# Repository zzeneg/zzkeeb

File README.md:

# zzkeeb

Shared library for my keyboard components

## KiCad

#### Installation
Go to KiCad, `Preferences` -> `Configure Paths`, add new row with name `ZZKEEB` and path to `zzkeeb/kicad`

#### Included projects

- https://github.com/sadekbaroudi/fingerpunch
- https://github.com/foostan/kbd
- https://github.com/crides/kleeb
- https://github.com/keebio/Keebio-Parts.pretty
- https://github.com/0xCB-dev/0xCB-libs
- https://github.com/Fooblitzky/DCS_keycaps.git

#### Additional 3D models

- [Encoder knob](https://grabcad.com/library/knob-85)
- [11mm rotary encoder](https://grabcad.com/library/11mm-metal-shaft-rotary-encoders-tht-vertical-w-push-on-switch-1)
- [ChocV1 socket](https://grabcad.com/library/kailh-1350-socket-2)
- [FFC horizontal 12p](https://grabcad.com/library/fpc-ffc-1)
- [KS-33 switch/socket](https://github.com/DeltaWhy/ols)
- [5way switch](https://grabcad.com/library/5-way-tactile-button-tht-1)
- [JST 12pin 1.25 connectors](https://grabcad.com/library/jst-gh-1-25mm-connector-set-1)

## Custom 3D models

- choc opener, just sprued two models from https://www.thingiverse.com/thing:3097933

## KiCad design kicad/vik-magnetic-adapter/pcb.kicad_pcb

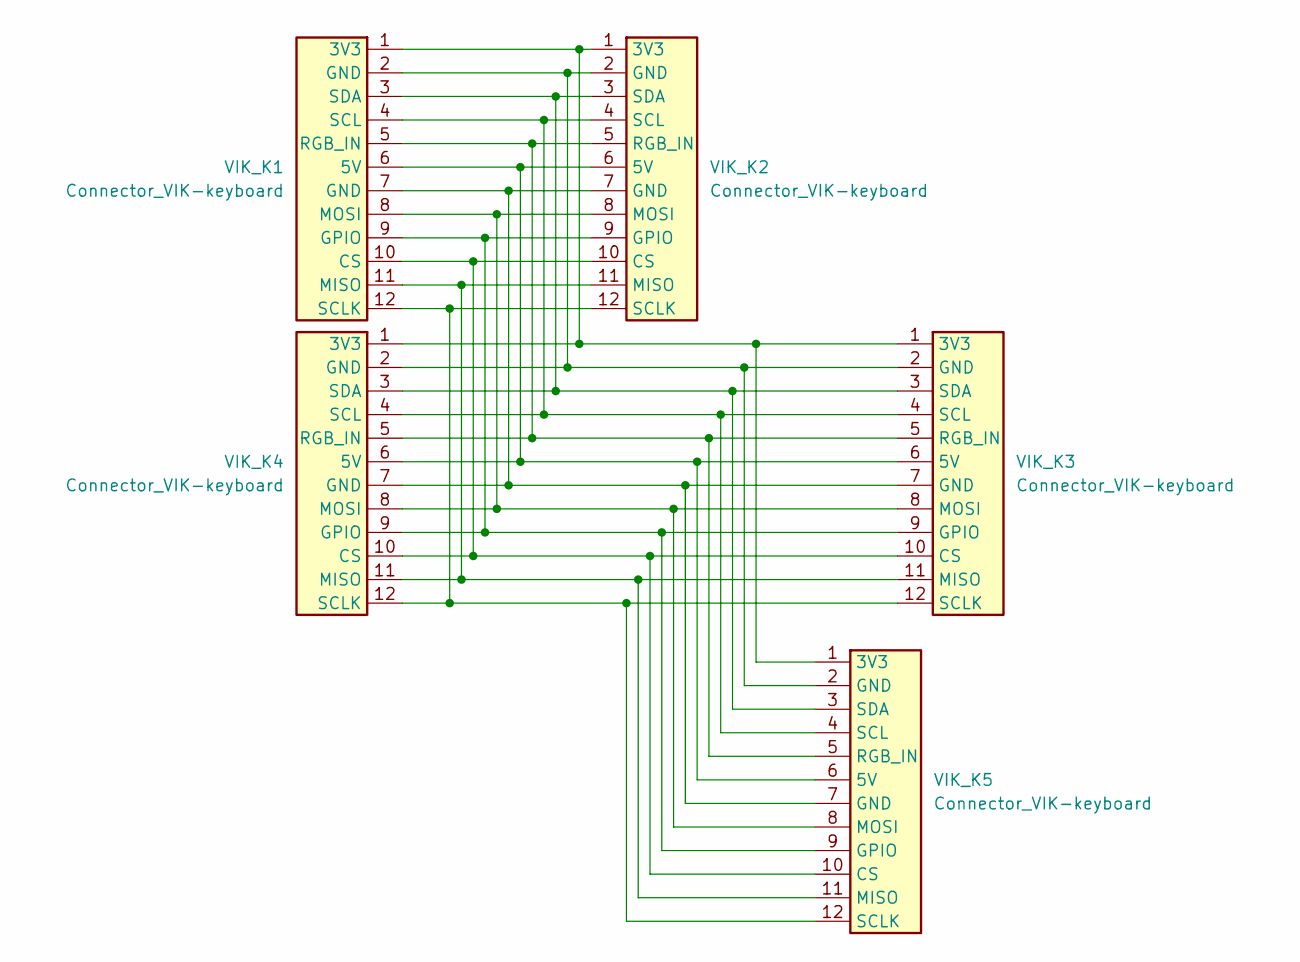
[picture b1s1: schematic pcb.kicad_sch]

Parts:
VIK_K1: Connector_VIK-keyboard; Connector_VIK-magnetic-keyboard
VIK_K2, VIK_K3: Connector_VIK-keyboard; Connector_VIK-vertical-keyboard
VIK_K4, VIK_K5: Connector_VIK-keyboard; Connector_VIK-horizontal-keyboard

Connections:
unnamed: VIK_K1.1 (3V3), VIK_K2.1 (3V3), VIK_K3.1 (3V3), VIK_K4.1 (3V3), VIK_K5.1 (3V3)
unnamed: VIK_K1.6 (5V), VIK_K2.6 (5V), VIK_K3.6 (5V), VIK_K4.6 (5V), VIK_K5.6 (5V)
unnamed: VIK_K1.10 (CS), VIK_K2.10 (CS), VIK_K3.10 (CS), VIK_K4.10 (CS), VIK_K5.10 (CS)
unnamed: VIK_K1.2 (GND), VIK_K2.2 (GND), VIK_K3.2 (GND), VIK_K4.2 (GND), VIK_K5.2 (GND)
unnamed: VIK_K1.7 (GND), VIK_K2.7 (GND), VIK_K3.7 (GND), VIK_K4.7 (GND), VIK_K5.7 (GND)
unnamed: VIK_K1.9 (GPIO), VIK_K2.9 (GPIO), VIK_K3.9 (GPIO), VIK_K4.9 (GPIO), VIK_K5.9 (GPIO)
unnamed: VIK_K1.11 (MISO), VIK_K2.11 (MISO), VIK_K3.11 (MISO), VIK_K4.11 (MISO), VIK_K5.11 (MISO)
unnamed: VIK_K1.8 (MOSI), VIK_K2.8 (MOSI), VIK_K3.8 (MOSI), VIK_K4.8 (MOSI), VIK_K5.8 (MOSI)
unnamed: VIK_K1.5 (RGB_IN), VIK_K2.5 (RGB_IN), VIK_K3.5 (RGB_IN), VIK_K4.5 (RGB_IN), VIK_K5.5 (RGB_IN)
unnamed: VIK_K1.4 (SCL), VIK_K2.4 (SCL), VIK_K3.4 (SCL), VIK_K4.4 (SCL), VIK_K5.4 (SCL)
unnamed: VIK_K1.12 (SCLK), VIK_K2.12 (SCLK), VIK_K3.12 (SCLK), VIK_K4.12 (SCLK), VIK_K5.12 (SCLK)
unnamed: VIK_K1.3 (SDA), VIK_K2.3 (SDA), VIK_K3.3 (SDA), VIK_K4.3 (SDA), VIK_K5.3 (SDA)

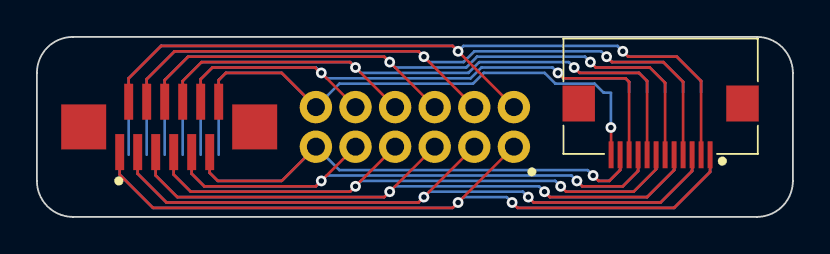
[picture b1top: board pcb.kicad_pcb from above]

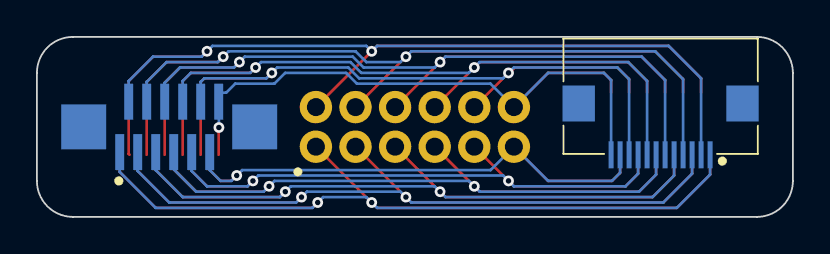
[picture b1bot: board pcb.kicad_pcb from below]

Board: 2 copper layers, 42.0 x 10.0 mm, 5 parts (2 on the bottom side), 12 nets.

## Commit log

2023-01-15 add kicad components
2023-01-19 improve and add components, add test project
2023-01-21 add cirque adapter
2023-02-03 improve choc footprint
2023-02-03 add kicad libraries
2023-02-03 more non-reversible footprints
2023-02-03 rp2040 zero
2023-02-03 add breakaway tabs
2023-02-03 improve 3d
2023-02-04 improve encoders and cirque
2023-02-04 small updates
2023-02-04 add choc socket model
2023-02-05 add symbols
2023-02-05 update symbols
2023-02-05 8 pin connector
2023-02-05 experimental ffc-fpc footprints
2023-02-05 small improvements
2023-02-06 fix trrs
2023-02-06 improve cirque adapter
2023-02-06 improve mid mount
2023-02-09 update footprints after testing
2023-02-10 new cutouts
2023-02-10 restore 3d models for reversible
2023-02-10 more cutouts
2023-02-11 flipped 3d models
2023-02-16 MX 3d models
2023-02-16 use original 3d models
2023-02-16 rename cutouts
2023-02-16 add more XIAO symbols/footprints
2023-02-16 small adjustments
2023-02-16 fix 3d models for standard components
2023-02-17 fix MXChocV2 footprints
2023-02-18 fix pica logo footprint
2023-02-18 add flipped 3d model for reversible choc
2023-02-21 new test components
2023-02-24 update usb connector
2023-02-26 improve rotary encoder
2023-03-01 improve ffc connector
2023-03-02 update logos
2023-03-06 fix choc top cutout
2023-03-07 update logo
2023-03-09 remove unused lib
2023-05-31 add gateron ks27/ks33 footprint
2023-06-02 improve ks switches
2023-06-02 add vik symbols
2023-06-03 add labeled symbols/footprints
2023-06-04 change label positions
2023-06-05 add ks-33 3D models and cutouts
2023-06-05 fix adapter footprint
2023-06-14 add fingerpunch lib
2023-06-14 update VIK footprints
2023-06-14 add MX-KS top cutout
2023-06-17 update MX-KS cutout
2023-06-24 Fix VIK placement
2023-07-07 increase font size, fix led
2023-07-09 improve MXKS cutout
2023-07-14 add choc opener
2023-07-18 update labels
2023-07-23 loosen MX cutouts
2023-08-13 add VIK adapter for magnetic connector
2023-08-19 5way switch and 6mm push button
2023-08-26 improve reversible footprints
2023-08-27 fix diodes 3D models
2023-08-27 5way 3d
2023-08-30 add magnetic adapter pcb
2023-09-01 update 5way knob
2023-09-01 loosen come cutouts
2023-09-04 add 3d models for magnetic connectors
2023-09-07 MCU footprints
2023-09-13 improve cutouts
2023-09-16 fix 5way reversible footprints
2023-09-19 update choc cutouts
2023-09-22 update 5way knobs
2023-10-28 improve rp zero footprint and choc cutout
2023-11-01 wireless components
2023-11-02 12 pin jst connectors
2023-11-05 fix n!n
2023-11-05 add SW_SPST_SKQG_WithoutStem
2023-11-05 add Alps 5way
2023-11-07 fix rp2040
2023-11-09 add fusion dance logo
2023-11-09 add M2 TH
2023-11-21 rotate alps 5way
2023-11-25 add FFC 12pin 1mm connector
2023-11-28 add FFC 12pin 1mm horizontal connector
2023-11-28 update 12pin connectors
2023-12-01 improve choc bottom cutout
2023-12-09 support smd 5way
2023-12-09 improve nice-nano footprint
2023-12-11 add ec12 model
2024-01-01 improve vertical ffc
2024-01-02 fix rp2040 zero
2024-01-08 add KS-minY footprint
2024-01-13 add vik
2024-01-15 add pmw3360 model
2024-02-03 add azoteq 3d models
2024-02-03 add s8050 and solder nut
2024-02-03 add display 12pin connector
2024-02-03 add vik module vertical
2024-02-08 update Cirque 40mm model
2024-02-09 add display connector 0.8mm pitch
2024-02-10 improve chocV2 cutout
2024-02-10 improve xiao footprints
2024-02-10 improve diode footprints
2024-02-13 add MX minY footprints
2024-02-14 add KS minY reversible
2024-02-14 diode footprints without labels
2024-02-14 fix reversible footprints
2024-02-15 improve MX/KS reversible
2024-02-16 mirrored footprints
2024-02-20 official azoteq models
2024-02-24 update solder nut footprint
2024-04-15 - KiCad 8 - add helios-like MCU footprint - add generic 12pin FFC connector footprints - improve minY footprints - add EC12 models
2024-04-24 update VIK connectors
2024-05-08 new footprints and models
2024-05-30 enlarge M2 holes
2024-06-11 fix reset button 3d model
2024-10-04 remove outdated VIK symbols
2024-11-01 add mx-ks-chocV2 footprint
2024-11-02 improve ffc 12pin vertical footprint for pcba
2024-11-17 add per56 encoder and full usb-c connector
2025-01-15 fix per56 encoder, add rp2040 tiny
2025-01-18 small fixes for choc v1 andd cheese footprints
